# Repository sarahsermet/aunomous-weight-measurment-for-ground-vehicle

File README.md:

# Weight Measurement for an Autonomous Ground Transportation Vehicle

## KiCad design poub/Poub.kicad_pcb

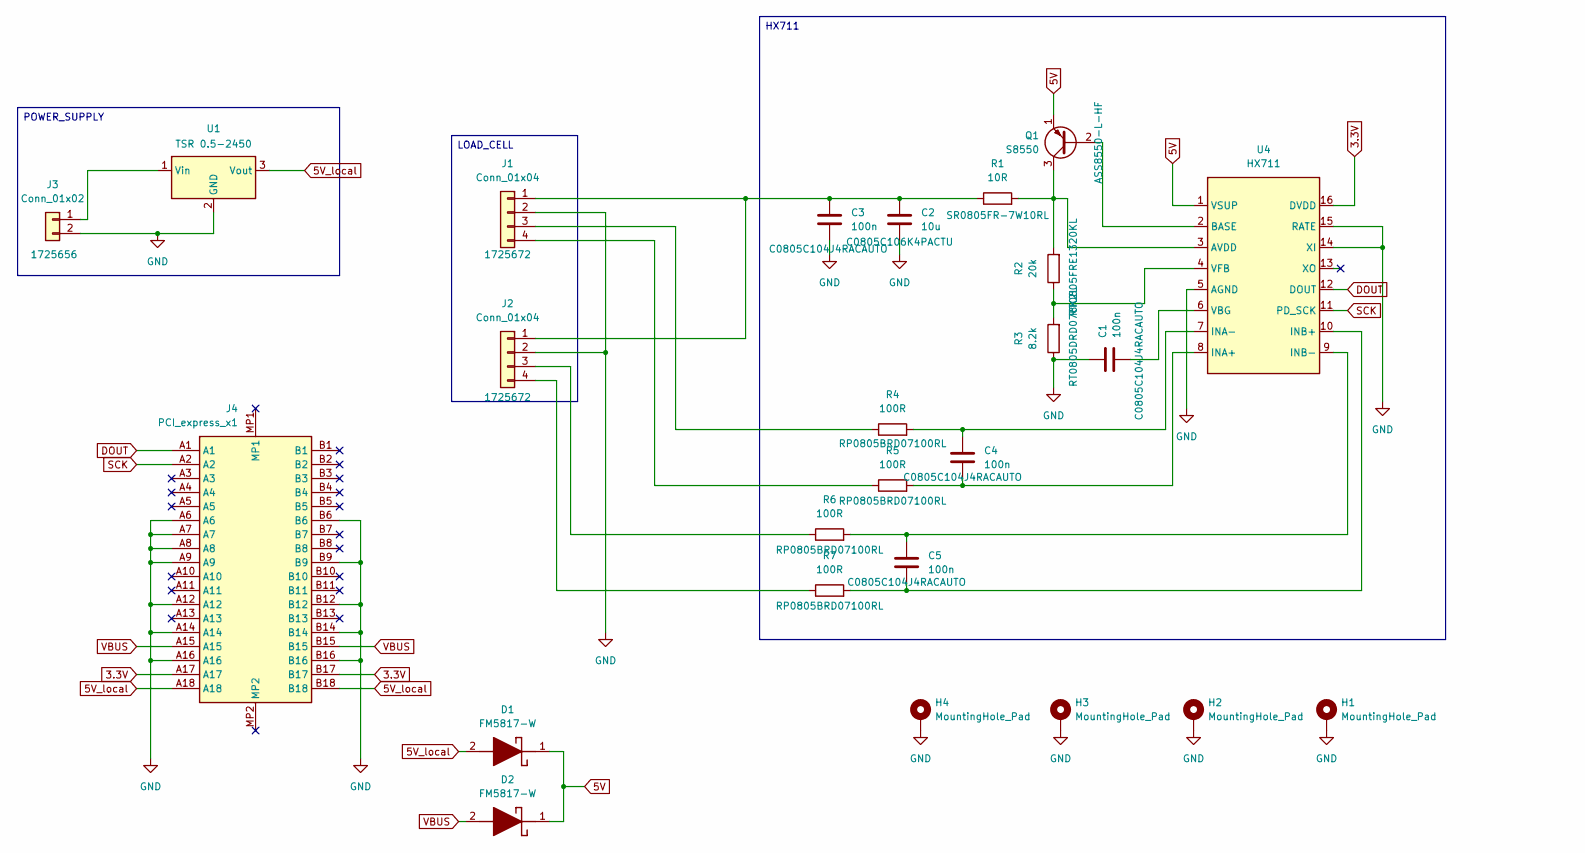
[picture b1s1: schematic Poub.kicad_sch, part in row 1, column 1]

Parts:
C1, C3, C4, C5: 100n; C_0805_2012Metric_Pad1.18x1.45mm_HandSolder
C2: 10u; C_0805_2012Metric_Pad1.18x1.45mm_HandSolder
D1, D2: FM5817-W; DIOM5025X231N; Manufacturer_Part_Number FM5817-W
H1, H2, H3, H4: MountingHole_Pad; MountingHole_3.2mm_M3_DIN965_Pad
J1, J2: Conn_01x04; TerminalBlock_Xinya_XY308-2.54-4P_1x04_P2.54mm_Horizontal
J3: Conn_01x02; TerminalBlock_Xinya_XY308-2.54-2P_1x02_P2.54mm_Horizontal
J4: PCI_express_x1; 10061913110CLF; Mouser Part Number 649-10061913-110CLF
Q1: S8550; SOT-23-3
R1: 10R; R_0805_2012Metric_Pad1.20x1.40mm_HandSolder
R2: 20k; R_0805_2012Metric_Pad1.20x1.40mm_HandSolder
R3: 8.2k; R_0805_2012Metric_Pad1.20x1.40mm_HandSolder
R4, R5, R6, R7: 100R; R_0805_2012Metric_Pad1.20x1.40mm_HandSolder
U1: Converter_DCDC_TRACO_TSR0.5-24xx_TSR0.5-24xxx_THT
U4: HX711; SOIC-16_3.9x9.9mm_P1.27mm

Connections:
3.3V: J4.A17, J4.B17, U4.16 (DVDD)
5V: D1.1 (K), D2.1 (K), Q1.1 (E), U4.1 (VSUP)
5V_local: D1.2 (A), J4.A18, J4.B18, U1.3 (Vout)
DOUT: J4.A1, U4.12 (DOUT)
GND: C1.1, C2.2, C3.2, H1.1, H2.1, H3.1, H4.1, J1.2, J2.2, J3.2, J4.A6, J4.A7, J4.A8, J4.A9, J4.A12, J4.A14, J4.A16, J4.B6, J4.B9, J4.B12, J4.B14, J4.B16, R3.1, U1.2 (GND), U4.5 (AGND), U4.14 (XI), U4.15 (RATE)
unnamed: C2.1, C3.1, J1.1, J2.1, R1.1
unnamed: J1.3, R4.1
unnamed: J1.4, R5.1
unnamed: J2.3, R6.1
unnamed: J2.4, R7.1
unnamed: J3.1, U1.1 (Vin)
unnamed: Q1.2 (B), U4.2 (BASE)
unnamed: Q1.3 (C), R1.2, R2.2, U4.3 (AVDD)
unnamed: C4.2, R5.2, U4.8 (INA+)
unnamed: C4.1, R4.2, U4.7 (INA-)
unnamed: C5.2, R7.2, U4.10 (INB+)
unnamed: C5.1, R6.2, U4.9 (INB-)
unnamed: C1.2, U4.6 (VBG)
unnamed: R2.1, R3.2, U4.4 (VFB)
SCK: J4.A2, U4.11 (PD_SCK)
VBUS: D2.2 (A), J4.A15, J4.B15

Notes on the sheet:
POWER_SUPPLY
HX711
LOAD_CELL

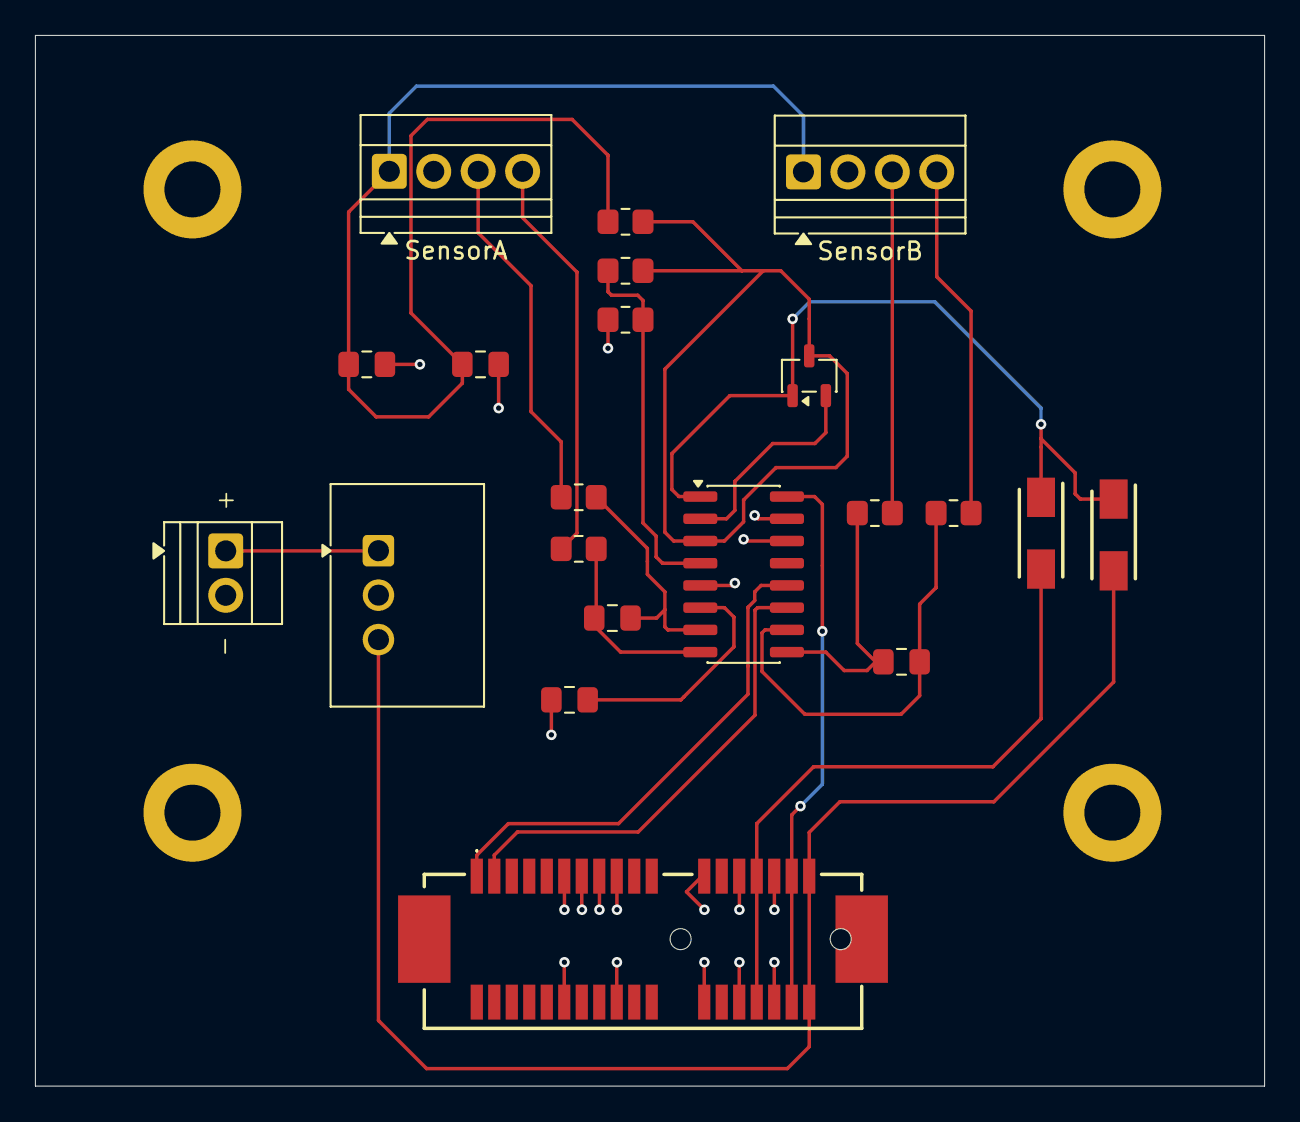
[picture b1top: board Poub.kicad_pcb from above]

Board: 4 copper layers, 70.2 x 60.0 mm, 25 parts (0 on the bottom side), 21 nets.

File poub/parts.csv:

"Reference","Qty","Value","DNP","Exclude from BOM","Exclude from Board","Footprint","Datasheet","Mfr. No","Mouser Part Number"
"C1","1","100n","","","","Capacitor_SMD:C_0805_2012Metric_Pad1.18x1.45mm_HandSolder","~","C0805C104J4RACAUTO",""
"C2","1","10u","","","","Capacitor_SMD:C_0805_2012Metric_Pad1.18x1.45mm_HandSolder","~","C0805C106K4PACTU",""
"C3","1","100n","","","","Capacitor_SMD:C_0805_2012Metric_Pad1.18x1.45mm_HandSolder","~","C0805C104J4RACAUTO",""
"C4","1","100n","","","","Capacitor_SMD:C_0805_2012Metric_Pad1.18x1.45mm_HandSolder","~","C0805C104J4RACAUTO",""
"C5","1","100n","","","","Capacitor_SMD:C_0805_2012Metric_Pad1.18x1.45mm_HandSolder","~","C0805C104J4RACAUTO",""
"D1","1","FM5817-W","","","","DIOM5025X231N","","FM5817-W",""
"D2","1","FM5817-W","","","","DIOM5025X231N","","FM5817-W",""
"J1","1","Conn_01x04","","","","TerminalBlock:TerminalBlock_Xinya_XY308-2.54-4P_1x04_P2.54mm_Horizontal","~","1725672",""
"J2","1","Conn_01x04","","","","TerminalBlock:TerminalBlock_Xinya_XY308-2.54-4P_1x04_P2.54mm_Horizontal","~","1725672",""
"J3","1","Conn_01x02","","","","TerminalBlock:TerminalBlock_Xinya_XY308-2.54-2P_1x02_P2.54mm_Horizontal","~","1725656",""
"J4","1","PCI_express_x1","","","","10061913110CLF","https://cdn.amphenol-cs.com/media/wysiwyg/files/documentatio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","10061913-110CLF","649-10061913-110CLF"
"Q1","1","S8550","","","","Package_TO_SOT_SMD:SOT-23-3","http://www.unisonic.com.tw/datasheet/S8550.pdf","ASS8550-L-HF",""
"R1","1","10R","","","","Resistor_SMD:R_0805_2012Metric_Pad1.20x1.40mm_HandSolder","~","SR0805FR-7W10RL ",""
"R2","1","20k","","","","Resistor_SMD:R_0805_2012Metric_Pad1.20x1.40mm_HandSolder","~","RT0805FRE1320KL",""
"R3","1","8.2k","","","","Resistor_SMD:R_0805_2012Metric_Pad1.20x1.40mm_HandSolder","~","RT0805DRD078K2L",""
"R4","1","100R","","","","Resistor_SMD:R_0805_2012Metric_Pad1.20x1.40mm_HandSolder","~","RP0805BRD07100RL",""
"R5","1","100R","","","","Resistor_SMD:R_0805_2012Metric_Pad1.20x1.40mm_HandSolder","~","RP0805BRD07100RL",""
"R6","1","100R","","","","Resistor_SMD:R_0805_2012Metric_Pad1.20x1.40mm_HandSolder","~","RP0805BRD07100RL",""
"R7","1","100R","","","","Resistor_SMD:R_0805_2012Metric_Pad1.20x1.40mm_HandSolder","~","RP0805BRD07100RL",""
"U1","1","~","","","","Converter_DCDC:Converter_DCDC_TRACO_TSR0.5-24xx_TSR0.5-24xxx_THT","https://www.tracopower.com/products/tsr0.5.pdf","TSR 0.5-2450",""

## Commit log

2026-04-29 load cell 100kg datasheet
2026-06-09 Add files via upload
    correction of some symbols and footprints
2026-06-09 final fabrication data
